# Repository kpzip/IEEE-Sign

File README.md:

# IEEE Sign

It's a sign that says "IEEE" using Argb lights. I don't know what more to say.

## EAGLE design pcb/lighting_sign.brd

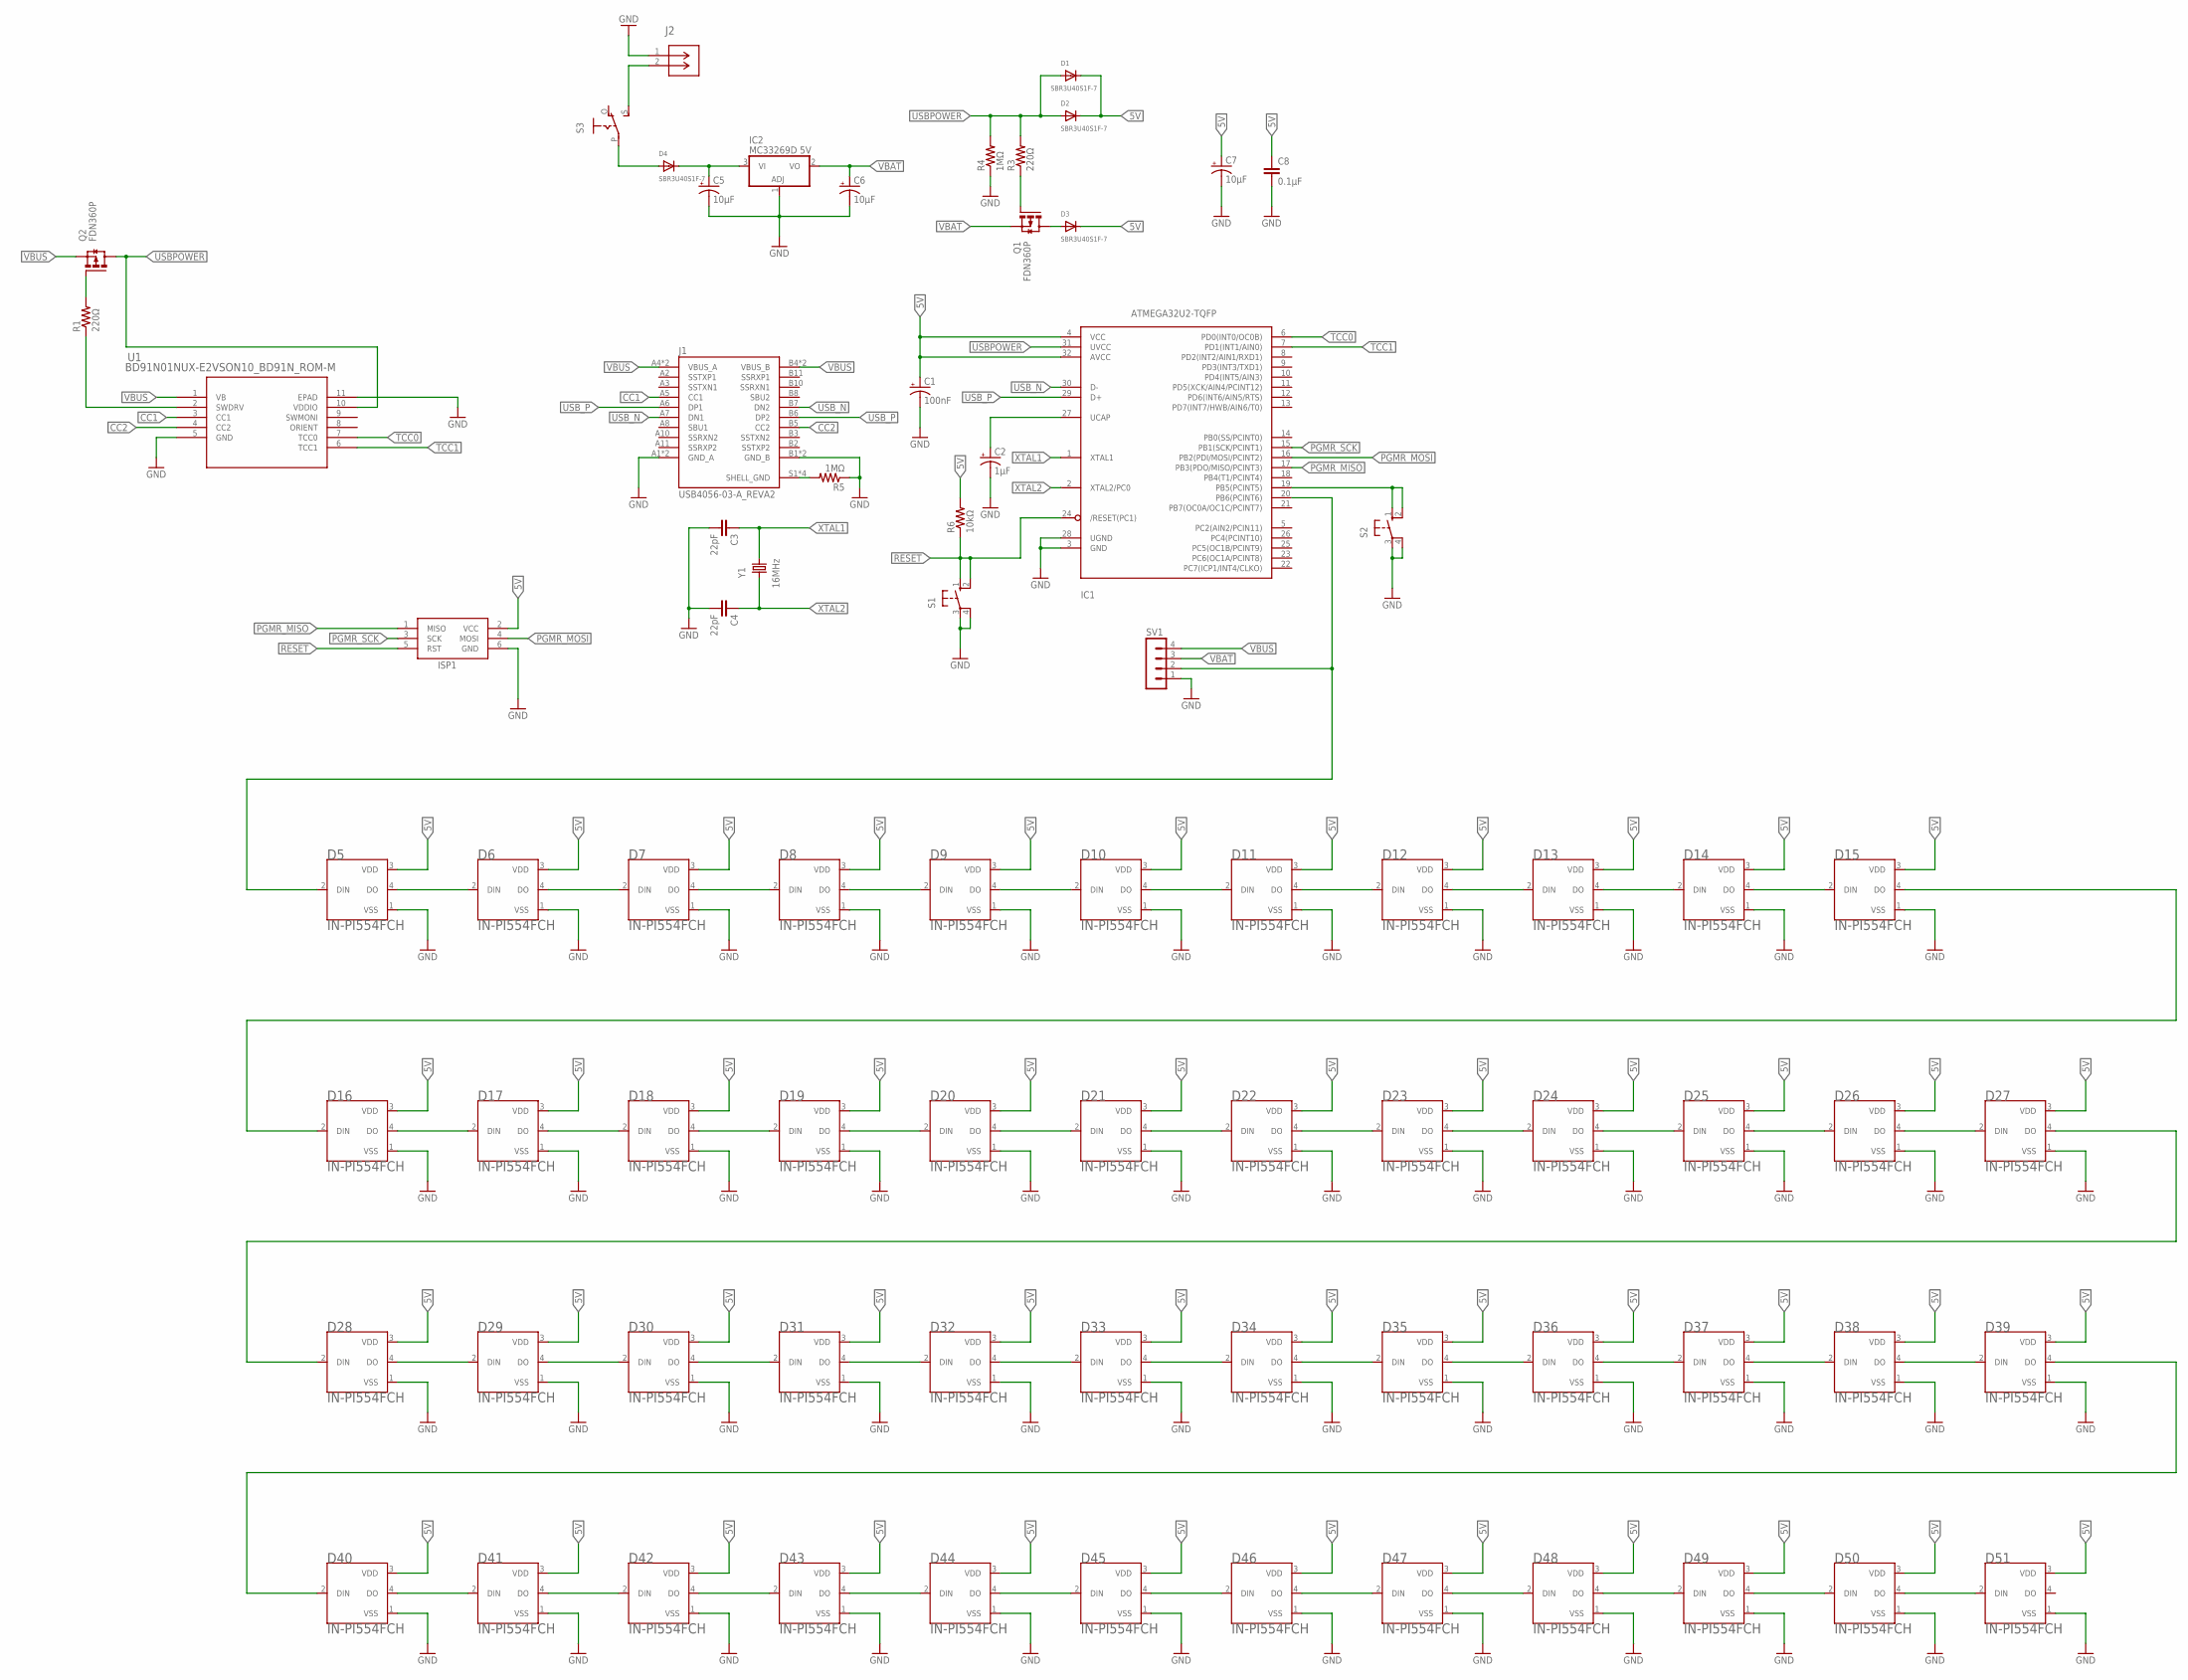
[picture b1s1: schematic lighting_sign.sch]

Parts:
C1: 100nF; PANASONIC_B
C2: 1µF; E2-5
C3, C4: 22pF; C0402
C5, C6, C7: 10µF; PANASONIC_B
C8: 0.1µF; C0402
D1, D2, D3, D4: SBR3U40S1F-7; SOD-123
D5, D6, D7, D8, D9, D10, D11, D12, D13, D14, D15, D16, D17, D18, D19, D20, D21, D22, D23, D24, D25, D26, D27, D28, D29, D30, D31, D32, D33, D34, D35, D36, D37, D38, D39, D40, D41, D42, D43, D44, D45, D46, D47, D48, D49, D50, D51: IN-PI554FCH; LED_IN-PI554FCH
IC1: ATMEGA32U2-TQFP; TQFP32-08
IC2: MC33269D 5V; DPACK
ISP1: AVRISP-BOX
J1: USB4056-03-A_REVA2; GCT_USB4056-03-A_REVA2
J2: BH9VPC 9V; CONN_BH9VPC_MPD
Q1, Q2: FDN360P; SUPER-SOT3
R1, R3: 220Ω; 0207/10
R4, R5: 1MΩ; 0207/10
R6: 10kΩ; 0207/10
S1, S2: 10-XX; B3F-10XX
S3: EG1218S; EG1218
SV1: MA04-1
U1: BD91N01NUX-E2VSON10_BD91N_ROM-M; VSON10_BD91N_ROM-M
Y1: 16MHz; HC49U-V

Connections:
5V: C1.+, C7.+, C8.1, D1.C, D2.C, D3.C, D5.3 (VDD), D6.3 (VDD), D7.3 (VDD), D8.3 (VDD), D9.3 (VDD), D10.3 (VDD), D11.3 (VDD), D12.3 (VDD), D13.3 (VDD), D14.3 (VDD), D15.3 (VDD), D16.3 (VDD), D17.3 (VDD), D18.3 (VDD), D19.3 (VDD), D20.3 (VDD), D21.3 (VDD), D22.3 (VDD), D23.3 (VDD), D24.3 (VDD), D25.3 (VDD), D26.3 (VDD), D27.3 (VDD), D28.3 (VDD), D29.3 (VDD), D30.3 (VDD), D31.3 (VDD), D32.3 (VDD), D33.3 (VDD), D34.3 (VDD), D35.3 (VDD), D36.3 (VDD), D37.3 (VDD), D38.3 (VDD), D39.3 (VDD), D40.3 (VDD), D41.3 (VDD), D42.3 (VDD), D43.3 (VDD), D44.3 (VDD), D45.3 (VDD), D46.3 (VDD), D47.3 (VDD), D48.3 (VDD), D49.3 (VDD), D50.3 (VDD), D51.3 (VDD), IC1.4 (VCC), IC1.32 (AVCC), ISP1.2 (VCC), R6.2
CC1: J1.A5 (CC1), U1.3 (CC1)
CC2: J1.B5 (CC2), U1.4 (CC2)
GND: C1.-, C2.-, C3.2, C4.2, C5.-, C6.-, C7.-, C8.2, D5.1 (VSS), D6.1 (VSS), D7.1 (VSS), D8.1 (VSS), D9.1 (VSS), D10.1 (VSS), D11.1 (VSS), D12.1 (VSS), D13.1 (VSS), D14.1 (VSS), D15.1 (VSS), D16.1 (VSS), D17.1 (VSS), D18.1 (VSS), D19.1 (VSS), D20.1 (VSS), D21.1 (VSS), D22.1 (VSS), D23.1 (VSS), D24.1 (VSS), D25.1 (VSS), D26.1 (VSS), D27.1 (VSS), D28.1 (VSS), D29.1 (VSS), D30.1 (VSS), D31.1 (VSS), D32.1 (VSS), D33.1 (VSS), D34.1 (VSS), D35.1 (VSS), D36.1 (VSS), D37.1 (VSS), D38.1 (VSS), D39.1 (VSS), D40.1 (VSS), D41.1 (VSS), D42.1 (VSS), D43.1 (VSS), D44.1 (VSS), D45.1 (VSS), D46.1 (VSS), D47.1 (VSS), D48.1 (VSS), D49.1 (VSS), D50.1 (VSS), D51.1 (VSS), IC1.3 (GND), IC1.28 (UGND), IC2.1 (ADJ), ISP1.6 (GND), J1.A1 (GND_A), J1.A12 (GND_A), J1.B1 (GND_B), J1.B12 (GND_B), J2.1, R4.1, R5.1, S1.3, S1.4 (P1), S2.3, S2.4 (P1), SV1.1, U1.5 (GND), U1.11 (EPAD)
unnamed: D3.A, Q1.3 (D)
unnamed: Q2.1 (G), R1.2
unnamed: Q1.1 (G), R3.1
unnamed: J2.2, S3.S
unnamed: C5.+, D4.C, IC2.3 (VI)
unnamed: D5.4 (DO), D6.2 (DIN)
unnamed: D6.4 (DO), D7.2 (DIN)
unnamed: D7.4 (DO), D8.2 (DIN)
unnamed: D8.4 (DO), D9.2 (DIN)
unnamed: D9.4 (DO), D10.2 (DIN)
unnamed: D10.4 (DO), D11.2 (DIN)
unnamed: D11.4 (DO), D12.2 (DIN)
unnamed: J1.S1 (SHELL_GND), J1.S2 (SHELL_GND), J1.S3 (SHELL_GND), J1.S4 (SHELL_GND), R5.2
unnamed: D5.2 (DIN), IC1.20 (PB6(PCINT6)), SV1.2
unnamed: C2.+, IC1.27 (UCAP)
unnamed: D4.A, S3.P
unnamed: IC1.19 (PB5(PCINT5)), S2.1 (S), S2.2 (S1)
unnamed: D12.4 (DO), D13.2 (DIN)
unnamed: D13.4 (DO), D14.2 (DIN)
unnamed: D14.4 (DO), D15.2 (DIN)
unnamed: D16.4 (DO), D17.2 (DIN)
unnamed: D17.4 (DO), D18.2 (DIN)
unnamed: D18.4 (DO), D19.2 (DIN)
unnamed: D19.4 (DO), D20.2 (DIN)
unnamed: D20.4 (DO), D21.2 (DIN)
unnamed: D21.4 (DO), D22.2 (DIN)
unnamed: D22.4 (DO), D23.2 (DIN)
unnamed: D15.4 (DO), D16.2 (DIN)
unnamed: D23.4 (DO), D24.2 (DIN)
unnamed: D24.4 (DO), D25.2 (DIN)
unnamed: D25.4 (DO), D26.2 (DIN)
unnamed: D26.4 (DO), D27.2 (DIN)
unnamed: D28.4 (DO), D29.2 (DIN)
unnamed: D29.4 (DO), D30.2 (DIN)
unnamed: D30.4 (DO), D31.2 (DIN)
unnamed: D31.4 (DO), D32.2 (DIN)
unnamed: D32.4 (DO), D33.2 (DIN)
unnamed: D33.4 (DO), D34.2 (DIN)
unnamed: D34.4 (DO), D35.2 (DIN)
unnamed: D27.4 (DO), D28.2 (DIN)
unnamed: D35.4 (DO), D36.2 (DIN)
unnamed: D36.4 (DO), D37.2 (DIN)
unnamed: D37.4 (DO), D38.2 (DIN)
unnamed: D38.4 (DO), D39.2 (DIN)
unnamed: D39.4 (DO), D40.2 (DIN)
unnamed: D40.4 (DO), D41.2 (DIN)
unnamed: D41.4 (DO), D42.2 (DIN)
unnamed: D42.4 (DO), D43.2 (DIN)
unnamed: D43.4 (DO), D44.2 (DIN)
unnamed: D44.4 (DO), D45.2 (DIN)
unnamed: D45.4 (DO), D46.2 (DIN)
unnamed: D46.4 (DO), D47.2 (DIN)
unnamed: D47.4 (DO), D48.2 (DIN)
unnamed: D48.4 (DO), D49.2 (DIN)
unnamed: D49.4 (DO), D50.2 (DIN)
unnamed: D50.4 (DO), D51.2 (DIN)
unnamed: R1.1, U1.2 (SWDRV)
PGMR_MISO: IC1.17 (PB3(PDO/MISO/PCINT3)), ISP1.1 (MISO)
PGMR_MOSI: IC1.16 (PB2(PDI/MOSI/PCINT2)), ISP1.4 (MOSI)
PGMR_SCK: IC1.15 (PB1(SCK/PCINT1)), ISP1.3 (SCK)
RESET: IC1.24 (/RESET(PC1)), ISP1.5 (RST), R6.1, S1.1 (S), S1.2 (S1)
TCC0: IC1.6 (PD0(INT0/OC0B)), U1.7 (TCC0)
TCC1: IC1.7 (PD1(INT1/AIN0)), U1.6 (TCC1)
USBPOWER: D1.A, D2.A, IC1.31 (UVCC), Q2.3 (D), R3.2, R4.2, U1.10 (VDDIO)
USB_N: IC1.30 (D-), J1.A7 (DN1), J1.B7 (DN2)
USB_P: IC1.29 (D+), J1.A6 (DP1), J1.B6 (DP2)
VBAT: C6.+, IC2.2 (VO), Q1.2 (S), SV1.3
VBUS: J1.A4 (VBUS_A), J1.A9 (VBUS_A), J1.B4 (VBUS_B), J1.B9 (VBUS_B), Q2.2 (S), SV1.4, U1.1 (VB)
XTAL1: C3.1, IC1.1 (XTAL1), Y1.2
XTAL2: C4.1, IC1.2 (XTAL2/PC0), Y1.1

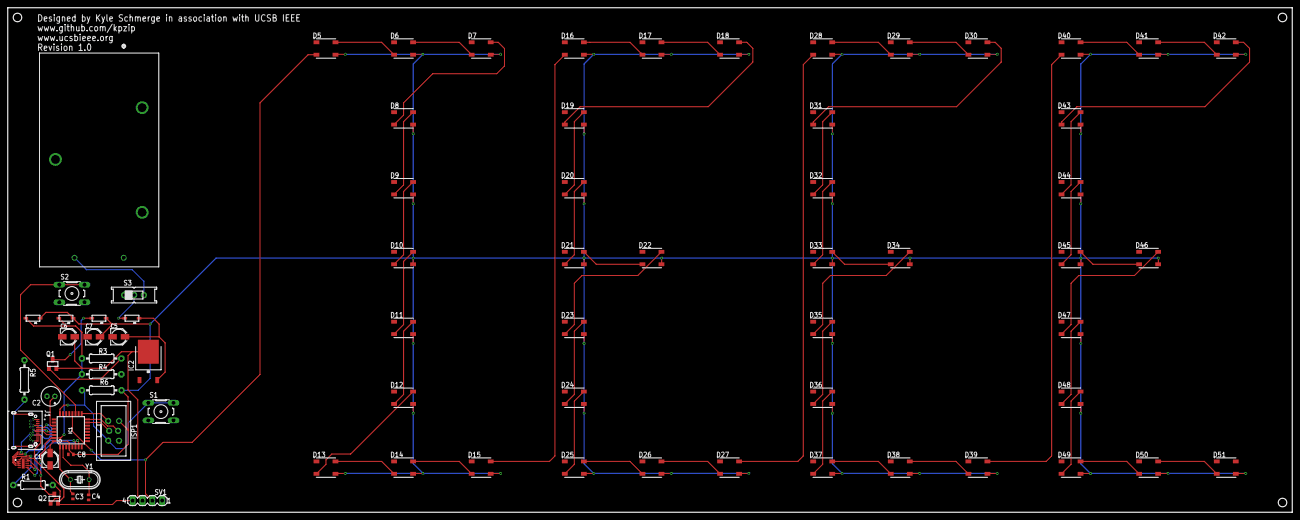
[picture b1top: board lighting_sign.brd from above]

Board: 2 copper layers, 331.0 x 130.0 mm, 77 parts (0 on the bottom side), 74 nets.

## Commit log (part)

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2025-05-27 stuff
2025-05-27 pcb files
2026-04-22 init
2026-04-22 schematic
2026-04-23 work

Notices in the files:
parts and their libraries:
COPYRIGHT: Copyright (C) 2024 Ultra Librarian. All rights reserved.
COPYRIGHT: Copyright (C) 2025 Ultra Librarian. All rights reserved.
